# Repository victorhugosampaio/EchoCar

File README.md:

# EchoCar

Hi there, my name is Victor. I'm a ~~undergraduate~~ graduated computer engineer, currently working as a firmware trainee engineer. The EchoCar is my final paper project for college.

I used two microcontrollers: a Bluepill (STM32F103C8T6) to control the hardware itself and an Arduino Nano 33 BLE Sense to run the MFCC algorithm and the AI model. I chose to use Zephyr as the RTOS to operate the system. To create and train the AI model and deploy it to the Arduino Nano microcontroller, I used Edge Impulse. I also used it to edit some audio data to fit within the 1-second window for training the model.

I used the Pete Warden voice dataset as the AI databse. The files used in this project can be accessed [here](https://drive.google.com/file/d/17HAxpKHDkPuj7wIeOMZ8yrCH6MHIF1b3/view?usp=sharing).

## Getting Started

Follow these instructions to set up and run the EchoCar project.

### Prerequisites

The project is divided into firmware and hardware.

For the hardware, check the project BOM for the required components.

```
STM32F103C8T6 microcontroller  
Arduino Nano 33 BLE Sense  
EchoCar's PCB  
2x 18650 batteries  
BOM components  
```

For the firmware, install the Zephyr RTOS and the Arduino IDE. You can follow the instructions on the Zephyr Getting Started page to install it on your machine and download the Arduino IDE from their website.

### Installing

After installing Zephyr, flash the firmware onto the STM32F103 using a flasher device such as the ST-Link v2.

First, build the project using:

```
west build -p
```

Then, flash it using:

```
west flash
```

For the Arduino firmware, install the EchoCar_inferencing.rar library in the Arduino IDE, then flash the .ino file to the Arduino Nano microcontroller.

## Built With

* [Zephyr RTOS](https://www.zephyrproject.org/) - The RTOS used.  
* [Edge Impulse](https://edgeimpulse.com/) - Used for AI model development.  
* [KiCad](https://www.kicad.org/) - Used to design the PCB.
* [Pete Warden Dataset](https://arxiv.org/pdf/1804.03209) - AI Dataset.

## Author

* **Victor Hugo Sampaio**

## Video
YouTube [link](https://youtu.be/iiWRqvPNBO4).

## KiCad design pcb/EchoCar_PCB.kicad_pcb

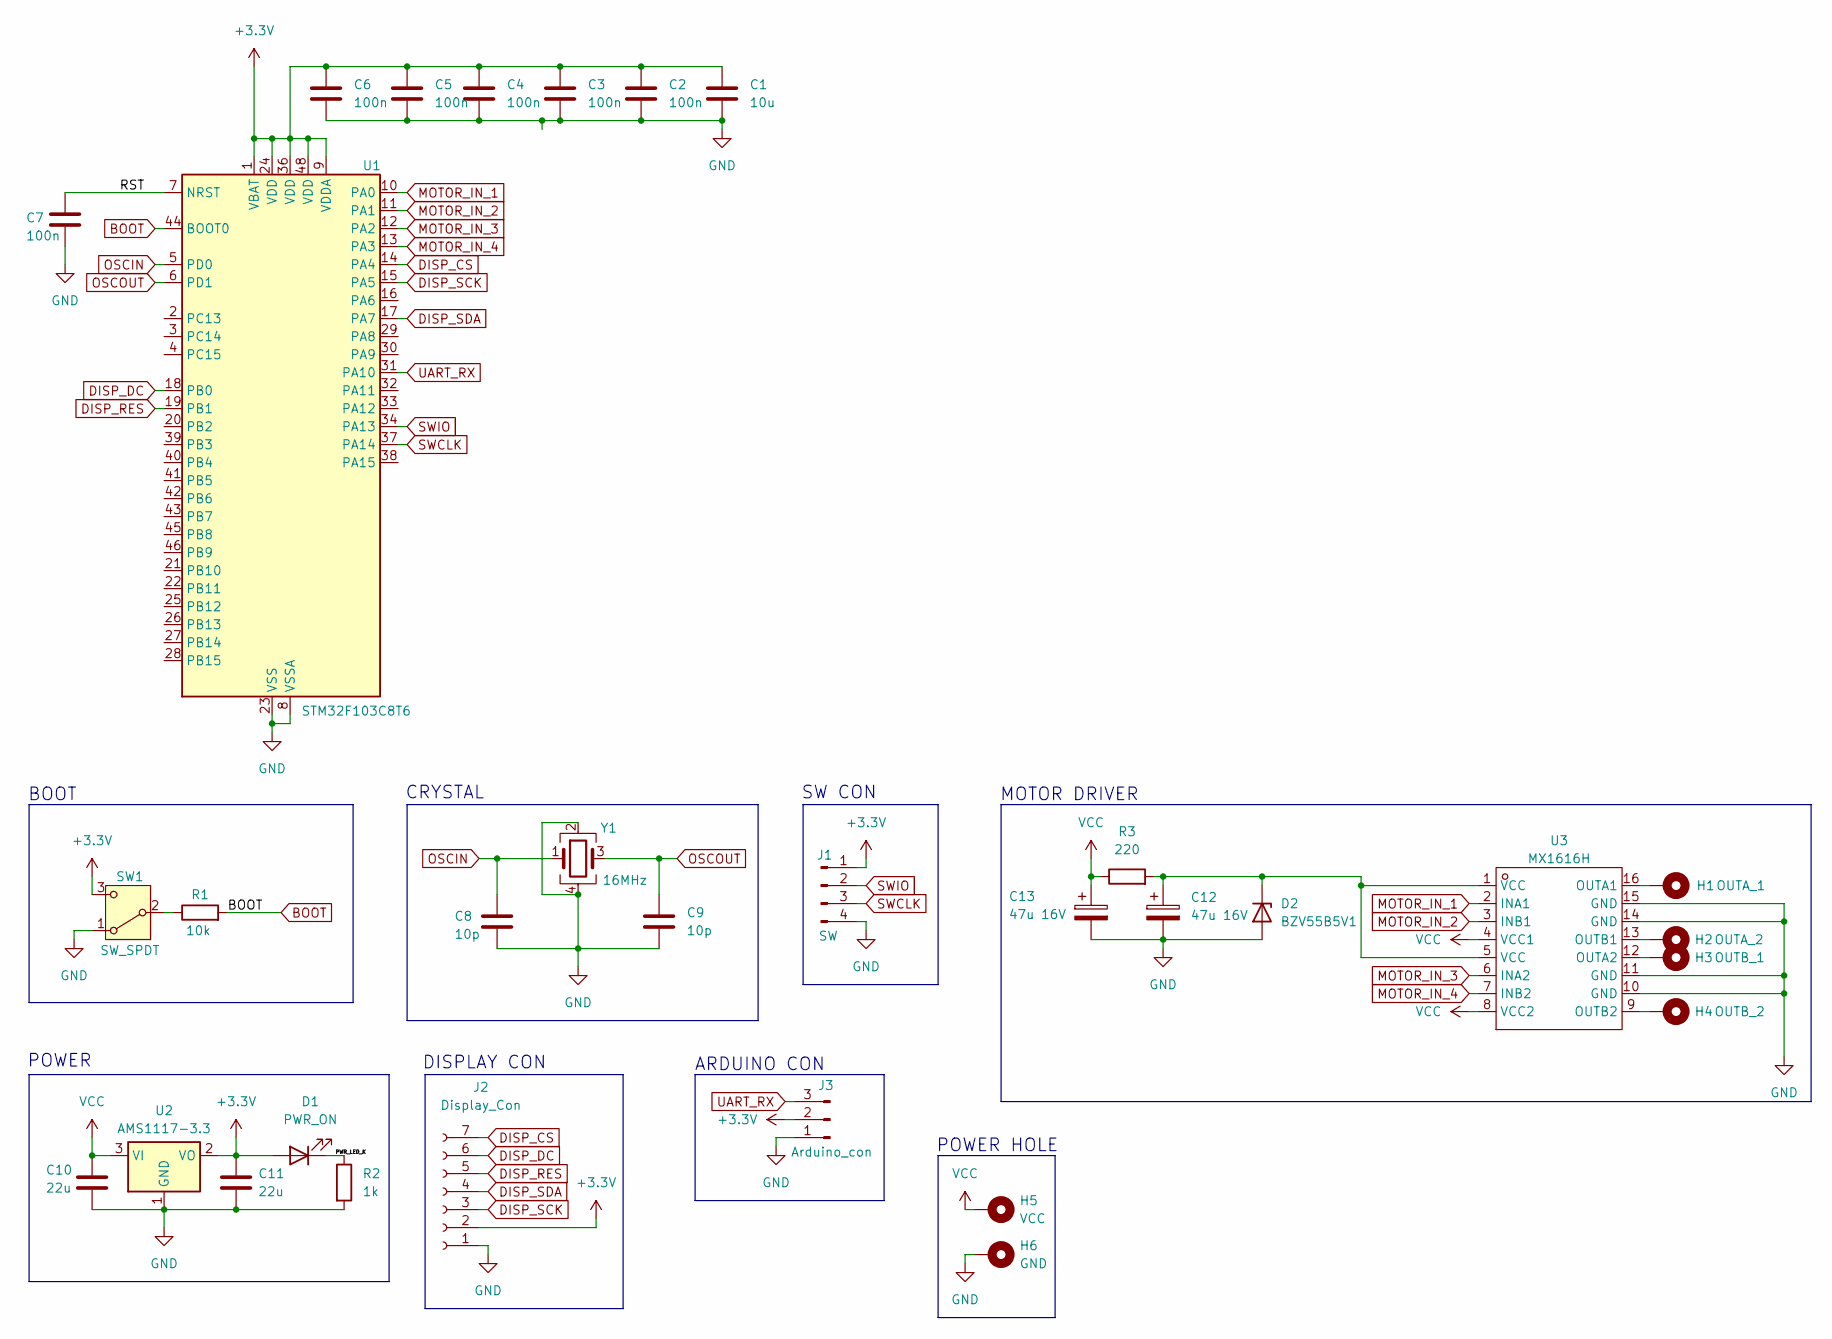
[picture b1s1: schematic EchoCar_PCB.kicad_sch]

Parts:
C1: 10u; C_0805_2012Metric
C2, C3, C4, C5, C6, C7: 100n; C_0402_1005Metric
C8, C9: 10p; C_0402_1005Metric
C10, C11: 22u; C_0805_2012Metric
C12, C13: 47u 16V; CP_Elec_5x5.3
D1: PWR_ON; LED_0603_1608Metric
D2: BZV55B5V1; D_MiniMELF
H1: OUTA_1; PinHeader_1x01_P2.54mm_Vertical
H2: OUTA_2; PinHeader_1x01_P2.54mm_Vertical
H3: OUTB_1; PinHeader_1x01_P2.54mm_Vertical
H4: OUTB_2; PinHeader_1x01_P2.54mm_Vertical
H5: VCC; PinHeader_1x01_P2.54mm_Vertical
H6: GND; PinHeader_1x01_P2.54mm_Vertical
J1: SW; PinHeader_1x04_P2.54mm_Vertical
J2: Display_Con; PinSocket_1x07_P2.54mm_Vertical
J3: Arduino_con; PinHeader_1x03_P2.54mm_Vertical
R1: 10k; R_0402_1005Metric
R2: 1k; R_0402_1005Metric
R3: 220; R_0402_1005Metric
SW1: SW_SPDT; SW_E-Switch_EG1224_SPDT_Angled
U1: STM32F103C8T6; LQFP-48_7x7mm_P0.5mm
U2: AMS1117-3.3; SOT-223-3_TabPin2
U3: MX1616H; LCSC Part Name MX1616H
Y1: 16MHz; Crystal_SMD_3225-4Pin_3.2x2.5mm

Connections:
+3.3V: C1.1, C2.1, C3.1, C4.1, C5.1, C6.1, C11.1, D1.2 (A), J1.1, J2.2, J3.2, SW1.3 (C), U1.1 (VBAT), U1.9 (VDDA), U1.24 (VDD), U1.36 (VDD), U1.48 (VDD), U2.2 (VO)
/PWR_LED_K: D1.1 (K), R2.1
/RST: C7.1, U1.7 (NRST)
BOOT: R1.2, U1.44 (BOOT0)
DISP_CS: J2.7, U1.14 (PA4)
DISP_DC: J2.6, U1.18 (PB0)
DISP_RES: J2.5, U1.19 (PB1)
DISP_SCK: J2.3, U1.15 (PA5)
DISP_SDA: J2.4, U1.17 (PA7)
GND: C1.2, C2.2, C3.2, C4.2, C5.2, C6.2, C7.2, C8.2, C9.2, C10.2, C11.2, C12.2, C13.2, D2.2 (A), H6.1, J1.4, J2.1, J3.1, R2.2, SW1.1 (A), U1.8 (VSSA), U1.23 (VSS), U1.35 (VSS), U1.47 (VSS), U2.1 (GND), U3.10 (GND), U3.11 (GND), U3.14 (GND), U3.15 (GND), Y1.2, Y1.4
MOTOR_IN_1: U1.10 (PA0), U3.2 (INA1)
MOTOR_IN_2: U1.11 (PA1), U3.3 (INB1)
MOTOR_IN_3: U1.12 (PA2), U3.6 (INA2)
MOTOR_IN_4: U1.13 (PA3), U3.7 (INB2)
unnamed: C12.1, D2.1 (K), R3.2, U3.1 (VCC), U3.5 (VCC)
unnamed: R1.1, SW1.2 (B)
unnamed: H1.1, U3.16 (OUTA1)
unnamed: H3.1, U3.12 (OUTA2)
unnamed: H2.1, U3.13 (OUTB1)
unnamed: H4.1, U3.9 (OUTB2)
OSCIN: C8.1, U1.5 (PD0), Y1.1
OSCOUT: C9.1, U1.6 (PD1), Y1.3
SWCLK: J1.3, U1.37 (PA14)
SWIO: J1.2, U1.34 (PA13)
UART_RX: J3.3, U1.31 (PA10)
VCC: C10.1, C13.1, H5.1, R3.1, U2.3 (VI), U3.4 (VCC1), U3.8 (VCC2)

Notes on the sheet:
ARDUINO CON
CRYSTAL
BOOT
POWER HOLE
POWER
MOTOR DRIVER
DISPLAY CON
SW CON

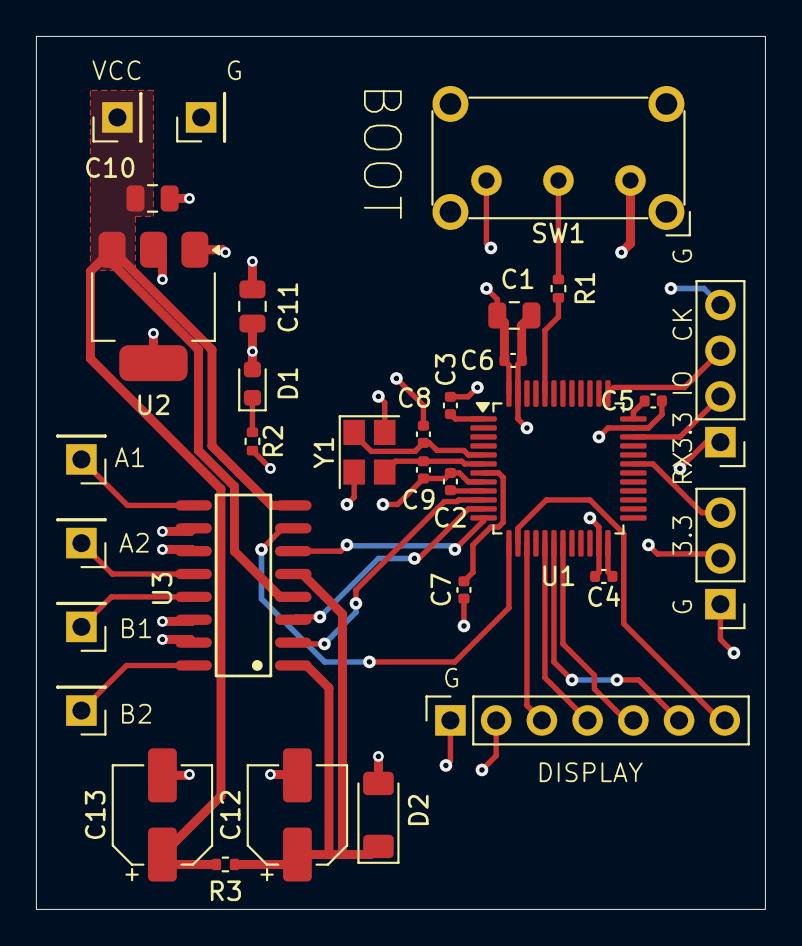
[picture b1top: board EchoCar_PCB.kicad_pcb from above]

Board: 4 copper layers, 40.5 x 48.5 mm, 32 parts (0 on the bottom side), 26 nets.

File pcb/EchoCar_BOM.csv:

Reference,Value,Link,Footprint,Qty
C1,10u,https://www.lcsc.com/product-detail/Multilayer-Ceramic-Capac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,Capacitor_SMD:C_0805_2012Metric,1
"C2,C3,C4,C5,C6,C7",100n,https://www.lcsc.com/product-detail/Multilayer-Ceramic-Capac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,Capacitor_SMD:C_0402_1005Metric,6
"C8,C9",10p,https://www.lcsc.com/product-detail/Multilayer-Ceramic-Capac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,Capacitor_SMD:C_0402_1005Metric,2
"C10,C11",22u,https://www.lcsc.com/product-detail/Multilayer-Ceramic-Capac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,Capacitor_SMD:C_0805_2012Metric,2
"C12,C13",47u 16V,https://www.lcsc.com/product-detail/Aluminum-Electrolytic-Ca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,Capacitor_SMD:CP_Elec_5x5.3,2
D1,PWR_ON,https://www.lcsc.com/product-detail/LED-Indication-Discrete_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,LED_SMD:LED_0603_1608Metric,1
D2,BZV55B5V1,https://www.lcsc.com/product-detail/Zener-Diodes_EIC-Semicon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,Diode_SMD:D_MiniMELF,1
J1,SW,x,Connector_PinHeader_2.54mm:PinHeader_1x04_P2.54mm_Vertical,1
J2,Display_Con,x,Connector_PinSocket_1.00mm:PinSocket_1x07_P2.54mm_Vertical,1
J3,Arduino_con,x,Connector_PinHeader_2.54mm:PinHeader_1x03_P2.54mm_Vertical,1
R1,10k,https://www.lcsc.com/product-detail/Chip-Resistor-Surface-Mo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,Resistor_SMD:R_0402_1005Metric,1
R2,1k,https://www.lcsc.com/product-detail/Chip-Resistor-Surface-Mo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,Resistor_SMD:R_0402_1005Metric,1
R3,220,https://www.lcsc.com/product-detail/Chip-Resistor-Surface-Mo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,Resistor_SMD:R_0402_1005Metric,1
SW1,SW_SPDT,https://www.lcsc.com/product-detail/Slide-Switches_XKB-Conne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,Button_Switch_THT:SW_E-Switch_EG1224_SPDT_Angled,1
U1,STM32F103C8T6,https://www.lcsc.com/product-detail/Microcontrollers-MCU-MPU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,Package_QFP:LQFP-48_7x7mm_P0.5mm,1
U2,AMS1117-3.3,https://www.lcsc.com/product-detail/Voltage-Regulators-Linea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,Package_TO_SOT_SMD:SOT-223-3_TabPin2,1
U3,MX1616H,https://www.lcsc.com/product-detail/Brushed-DC-Motor-Drivers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,MX1616H_SMD:MX1616H,1
Y1,16MHz,https://www.lcsc.com/product-detail/Crystals_Shenzhen-SCTF-E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,Crystal:Crystal_SMD_3225-4Pin_3.2x2.5mm,1

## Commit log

2025-01-03 feat: Create the project base.
    Create the project first files.
2025-01-15 feat: Create the display driver.
    Create the display driver for the SPI 0.96'' OLED Display with the SSD1306 driver.
2025-01-21 refactor: Refactor the display driver.
    Change the 5x7 font to the 8x8 and adjust some code lines.
2025-01-21 feat: Create the motor driver.
    Create the motor driver for the L293D H driver.
2025-01-22 refactor: Refactor the code format.
    Adjust the clang-format file and refactor the code formart.
2025-01-22 feat: Create the car handler.
    Create the car handler.
2025-01-23 refactor: Finish the car handler.
    Adjust the motor driver and finish the car handler.
2025-01-23 fix: Fix changes.
    Fix name changes.
2025-01-23 fix: Overlay fix.
    Fix the board overlay file.
2025-01-23 refactor: Reformat the code.
    Reformat functions briefs and alocate defines in the Kconfig file.
2025-01-24 feat: Create the usart driver.
    Create the usart driver and adapt the car handler.
2025-01-24 fix: Fix the usart driver.
    Fix the usart driver.
2025-01-24 refactor: Remove includes.
    Remove unused includes.
2025-01-27 fix: Fix usart.
    Fix some usart bugs due to some default configurations.
2025-01-28 refactor: Adjust documentation.
    Adjust some documentation.
2025-01-31 chore: Improve the car handler.
    Optmize the car handler using tables.
2025-02-03 feat: Add the arduino files.
    Add the Nano BLE Sense files (UART and the ML model).
2025-02-05 feat: Complete the communication.
    Complete the communication comands via usart.
2025-02-11 feat: Create the PCB.
    Create the car pcb.
2025-02-17 feat: Add the MX1616H.
    Create the MX1616H footprint and symbol.
2025-02-17 feat: Add the motor driver.
    Add the motor driver to the schematic.
2025-02-20 feat: Conclude the schematic.
    Conclude the pcb schematic and add the BOM.
2025-02-26 feat: Finish the PCB.
    Finish the project PCB.
2025-02-26 Create the block diagram.
    Create the EchoCar PCB block diagram.
2025-03-19 feat: add the used scripts.
    Add the script used to select random samples.
2025-04-07 Add the project database.
2025-05-13 fix: fix car handler
    Fix time displaying on car handler.
